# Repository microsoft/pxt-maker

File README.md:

# MakeCode Maker 

This is an experimental code editor for maker boards - try it at https://maker.makecode.com.

* [Read the docs](https://maker.makecode.com/about)

## Who is this for?

This editor is meant for micro-controllers that are friendly to breadboarding. The editor is based on [Microsoft MakeCode](https://makecode.com).

## Local Dev Server

The local server lets you to run the editor and serve the documentation from your own computer.

### Setup

1. Install [Node.js](https://nodejs.org/) 8.9.4 or higher.
2. Install [Docker](https://www.docker.com/) if you are going to edit any `.cpp` files.
3. Clone the pxt repository.
```
git clone https://github.com/microsoft/pxt
cd pxt
```
4. Install the dependencies of ``Microsoft/pxt`` and build it
```
npm install
npm run build
cd ..
```
5. Clone the ``Microsoft/pxt-common-packages`` repository
```
git clone https://github.com/microsoft/pxt-common-packages
cd pxt-common-packages
npm install
cd ..
```
6. Clone the ``Microsoft/pxt-maker`` repository
```
git clone https://github.com/microsoft/pxt-maker
cd pxt-maker
```
7. Install the PXT command line (add `sudo` for Mac/Linux shells).
```
npm install -g pxt
```
8. Install the pxt-maker dependencies.
```
npm install
```
8. Link pxt-maker back to base pxt repo (add `sudo` for Mac/Linux shells).
```
rm -Rf node_modules/pxt-core
rm -Rf node_modules/pxt-common-packages
pxt link ../pxt
pxt link ../pxt-common-packages
```

If you want to know if your folders are link, run ``ls -l``
and it will indicate them.

```
ls -l node_modules/
```

Note the above command assumes the folder structure of   
```
       maker.makecode.com
          |
  ----------------------------------
  |       |                        |
 pxt      pxt-common-packages  pxt-maker
 ```

### Refresh dal.d.ts files

Whenever you make changes to the ``#defines`` in the .cpp files, you will have to refresh
the ``dal.d.ts`` files. For that, run

```
pxt builddaldts
```

### CODAL changes

If you need to do changes to CODAL itself, follow these steps.

* create a new project in the web editor, then close the web server. Select the hardware you want to work with.
* using a command prompt, open the ``projects`` folder and find the subfolder with your new project
* open the folder in Visual Studio Code
```
code .
```
* open ``pxt.json`` and edit the dependencies to use 
the ``file:...`` path instead of ``*``

```
   dependencies: {
        "adafruit-metro-m0-express": "file:../../libs/adafruit-metro-m0-express"
   }
```
* from the command line, set the ``PXT_NODOCKER`` environment variable to ``1``

```
export PXT_NODOCKER=1
```

* run a local build that will create a CODAL checkout automatically. 
If you are missing tools, you will be notified by the build script.

```
pxt build --local --force
```

* go to the ``built/dockercodal`` folder and open all CODAL in a new Visual Studio Code instance

```
cd built/dockercodal
code libraries/*
```

* go to the Git tab in VS Code, and change the branch of the CODAL repository to work on to ``master``. You can create a new branch to start doing your work and pull requests.

* to build CODAL directly, run ``built/codal``
```
python build.py
```

* to rebuild your project from pxt, run ``pxt build --local --force`` from the project folder

### Running

Run this command from inside pxt-maker to open a local web server
```
pxt serve
```
If the local server opens in the wrong browser, make sure to copy the URL containing the local token. 
Otherwise, the editor will not be able to load the projects.

If you need to modify the `.cpp` files (and have installed yotta), enable yotta compilation using the `--localbuild` flag:
```
pxt serve --localbuild
```

### Updates

Make sure to pull changes from all repos regularly. More instructions are at https://github.com/microsoft/pxt#running-a-target-from-localhost

## Repos 

The pxt-maker target depends on several other repos. The main ones are:
- https://github.com/microsoft/pxt, the PXT framework
- https://github.com/microsoft/pxt-commmon-packages, common APIs accross various MakeCode editors
- https://github.com/lancaster-university/codal-core, CODAL core project
- https://github.com/lancaster-university/codal-mbed, mbed layer
- https://github.com/lancaster-university/codal-samd21, CODAL SAMD21 layer
- https://github.com/lancaster-university/codal-circuit-playground, Adafruit CPX layer

## Code of Conduct

This project has adopted the [Microsoft Open Source Code of Conduct](https://opensource.microsoft.com/codeofconduct/). For more information see the [Code of Conduct FAQ](https://opensource.microsoft.com/codeofconduct/faq/) or contact [opencode@microsoft.com](mailto:opencode@microsoft.com) with any additional questions or comments.

# Contributing

This project welcomes contributions and suggestions.  Most contributions require you to agree to a
Contributor License Agreement (CLA) declaring that you have the right to, and actually do, grant us
the rights to use your contribution. For details, visit https://cla.microsoft.com.

When you submit a pull request, a CLA-bot will automatically determine whether you need to provide
a CLA and decorate the PR appropriately (e.g., label, comment). Simply follow the instructions
provided by the bot. You will only need to do this once across all repos using our CLA.

This project has adopted the [Microsoft Open Source Code of Conduct](https://opensource.microsoft.com/codeofconduct/).
For more information see the [Code of Conduct FAQ](https://opensource.microsoft.com/codeofconduct/faq/) or
contact [opencode@microsoft.com](mailto:opencode@microsoft.com) with any additional questions or comments.

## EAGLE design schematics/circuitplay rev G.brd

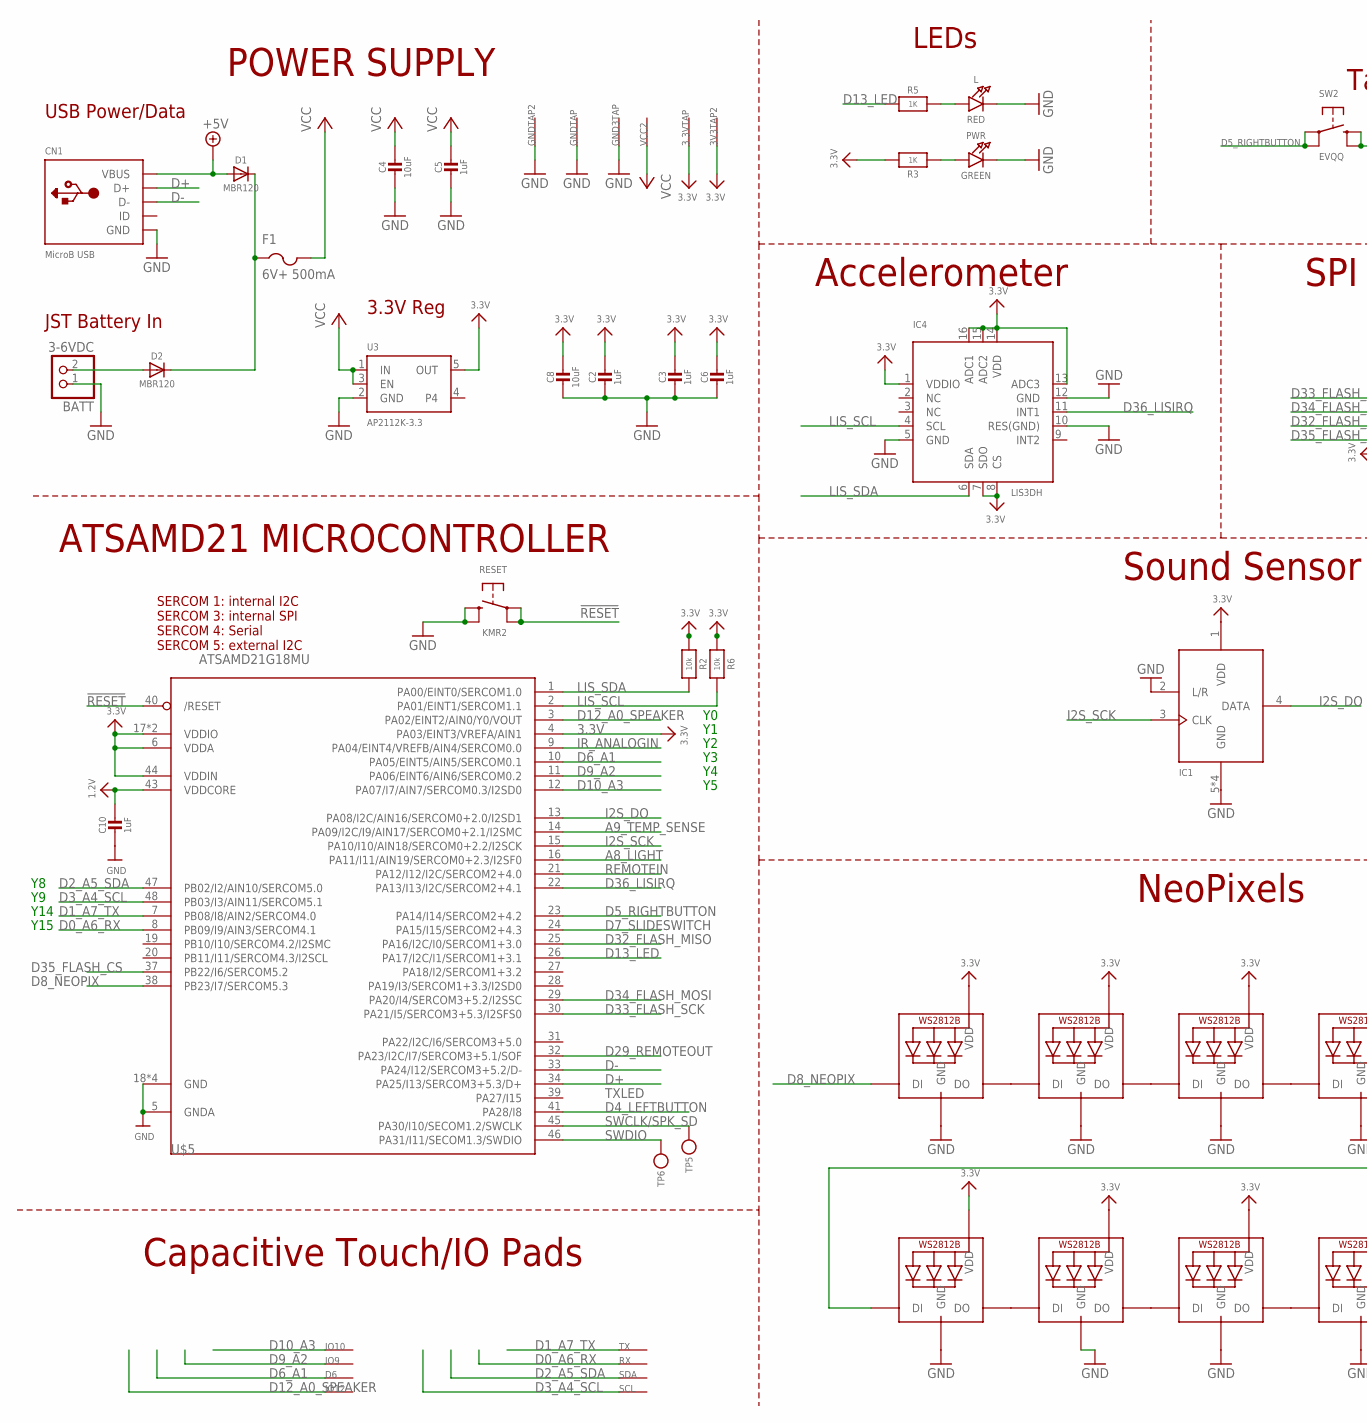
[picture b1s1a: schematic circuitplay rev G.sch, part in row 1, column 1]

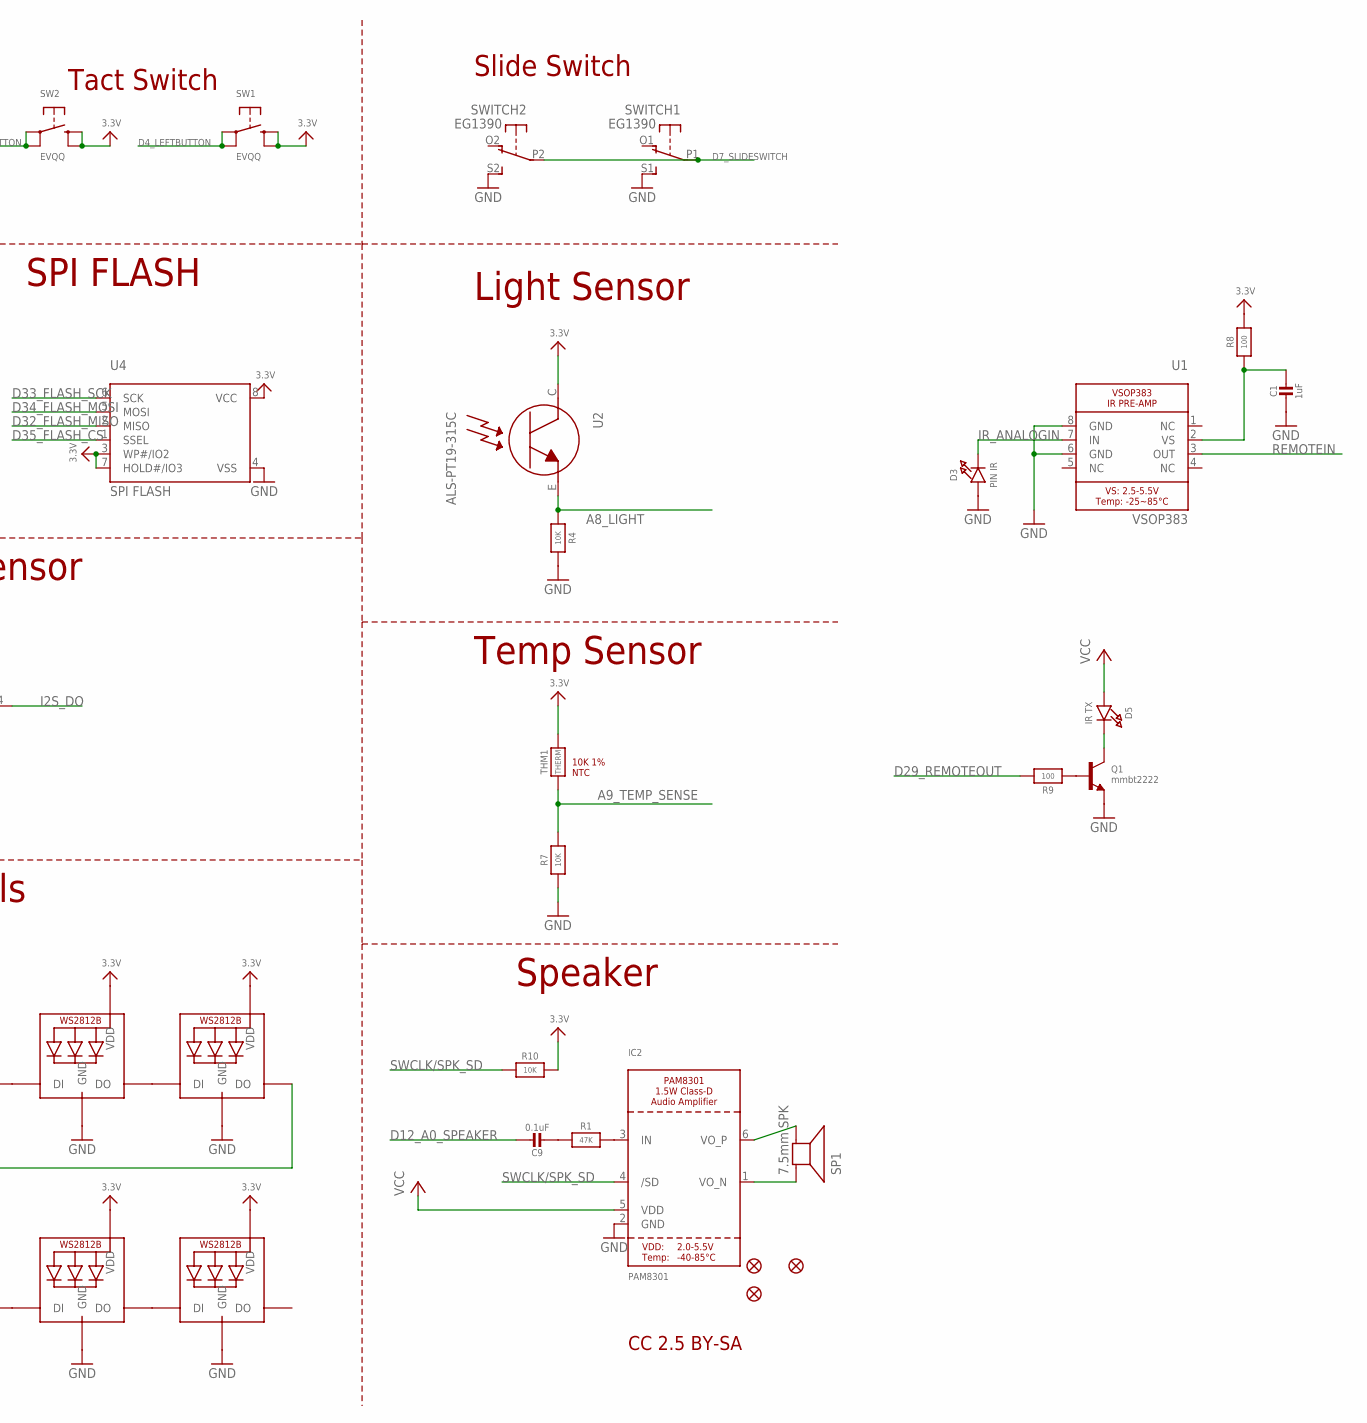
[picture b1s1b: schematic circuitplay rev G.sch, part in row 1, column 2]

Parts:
3.3VTAP, 3V3TAP2: SEWTAP-ALLIGATOR; SEWALLI
BATT: 3-6VDC; JSTPH2
C1, C2, C3, C5, C6, C10: 1uF; 0603-NO
C4, C8: 10uF; 0805-NO
C9: 0.1uF; 0603-NO
CN1: MicroB USB; 4UCONN_20329_V2
D1, D2: MBR120; SOD-123
D3: PIN IR; CHIPLED_1206_NOOUTLINE
D5: IR TX; CHIPLED_1206_NOOUTLINE
D6: SEWTAP-ALLIGATOR; SEWALLI
F1: 6V+ 500mA; R1206
GND3TAP: SEWTAP-ALLIGATOR; SEWALLI
GNDTAP, GNDTAP2: SEWTAP-ALLIGATOR; SEWALLI
IC1: MIC_PDM; SPK0415HM4H
IC2: PAM8301; SOT23-6
IC4: LIS3DH; LGA16_3X3MM
IO9, IO10, IO12: SEWTAP-ALLIGATOR; SEWALLI
L: RED; CHIPLED_0805_NOOUTLINE
LED1, LED2, LED3, LED4, LED5, LED6, LED7, LED8, LED9, LED10: WS2812B3535; LED3535
PWR: GREEN; CHIPLED_0805_NOOUTLINE
Q1: mmbt2222; SOT23-R
R1: 47K; 0603-NO
R2, R6: 10k; 0603-NO
R3, R5: 1K; 0603-NO
R4, R7, R10: 10K; 0603-NO
R8, R9: 100; 0603-NO
RESET: KMR2; BTN_KMR2_4.6X2.8
RX: SEWTAP-ALLIGATOR; SEWALLI
SCL: SEWTAP-ALLIGATOR; SEWALLI
SDA: SEWTAP-ALLIGATOR; SEWALLI
SP1: 7.5mm SPK; BUZZER_SMT_7.5MM
SW1, SW2: EVQQ; EVQ-Q2_SMALLER
SWITCH: EG1390
THM1: THERM; _0402
TP5, TP6: TESTPOINTROUND1.5MM; TESTPOINT_ROUND_1.5MM
TX: SEWTAP-ALLIGATOR; SEWALLI
U1: VSOP383
U2: ALS-PT19-315C
U3: AP2112K-3.3; SOT23-5
U4: SPI FLASH; SOIC8_150MIL
U$2, U$3, U$6: FIDUCIAL_1MM
U$5: ATSAMD21G18MU; TQFN48_7MM
VCC2: SEWTAP-ALLIGATOR; SEWALLI

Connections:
1.2V: C10.1, U$5.43 (VDDCORE)
3.3V: 3.3VTAP.P$1, 3V3TAP2.P$1, C2.1, C3.1, C6.1, C8.1, IC1.1 (VDD), IC4.1 (VDDIO), IC4.7 (SDO), IC4.8 (CS), IC4.13 (ADC3), IC4.14 (VDD), IC4.15 (ADC2), IC4.16 (ADC1), LED1.2 (VDD), LED2.2 (VDD), LED3.2 (VDD), LED4.2 (VDD), LED5.2 (VDD), LED6.2 (VDD), LED7.2 (VDD), LED8.2 (VDD), LED9.2 (VDD), LED10.2 (VDD), R2.1, R3.2, R6.1, R8.2, R10.2, SW1.B (S), SW1.B' (S1), SW2.B (S), SW2.B' (S1), THM1.2, U2.C, U3.5 (OUT), U4.3 (WP#/IO2), U4.7 (HOLD#/IO3), U4.8 (VCC), U$5.4 (PA03/EINT3/VREFA/AIN1), U$5.6 (VDDA), U$5.17 (VDDIO), U$5.36 (VDDIO), U$5.44 (VDDIN)
!RESET: RESET.A, RESET.A' (P1), U$5.40 (/RESET)
+5V: CN1.VBUS, D1.A
A8_LIGHT: R4.2, U2.E, U$5.16 (PA11/I11/AIN19/SERCOM0+2.3/I2SF0)
A9_TEMP_SENSE: R7.2, THM1.1, U$5.14 (PA09/I2C/I9/AIN17/SERCOM0+2.1/I2SMC)
D0_A6_RX: RX.P$1, U$5.8 (PB09/I9/AIN3/SERCOM4.1)
D1_A7_TX: TX.P$1, U$5.7 (PB08/I8/AIN2/SERCOM4.0)
D2_A5_SDA: SDA.P$1, U$5.47 (PB02/I2/AIN10/SERCOM5.0)
D3_A4_SCL: SCL.P$1, U$5.48 (PB03/I3/AIN11/SERCOM5.1)
D4_LEFTBUTTON: SW1.A, SW1.A' (P1), U$5.41 (PA28/I8)
D5_RIGHTBUTTON: SW2.A, SW2.A' (P1), U$5.23 (PA14/I14/SERCOM2+4.2)
D6_A1: D6.P$1, U$5.10 (PA05/EINT5/AIN5/SERCOM0.1)
D7_SLIDESWITCH: SWITCH.P1, SWITCH.P2, U$5.24 (PA15/I15/SERCOM2+4.3)
D8_NEOPIX: LED6.1 (DI), U$5.38 (PB23/I7/SERCOM5.3)
D9_A2: IO9.P$1, U$5.11 (PA06/EINT6/AIN6/SERCOM0.2)
D10_A3: IO10.P$1, U$5.12 (PA07/I7/AIN7/SERCOM0.3/I2SD0)
D12_A0_SPEAKER: C9.1, IO12.P$1, U$5.3 (PA02/EINT2/AIN0/Y0/VOUT)
D13_LED: R5.1, U$5.26 (PA17/I2C/I1/SERCOM1+3.1)
D29_REMOTEOUT: R9.2, U$5.32 (PA23/I2C/I7/SERCOM3+5.1/SOF)
D32_FLASH_MISO: U4.2 (MISO), U$5.25 (PA16/I2C/I0/SERCOM1+3.0)
D33_FLASH_SCK: U4.6 (SCK), U$5.30 (PA21/I5/SERCOM3+5.3/I2SFS0)
D34_FLASH_MOSI: U4.5 (MOSI), U$5.29 (PA20/I4/SERCOM3+5.2/I2SSC)
D35_FLASH_CS: U4.1 (SSEL), U$5.37 (PB22/I6/SERCOM5.2)
D36_LISIRQ: IC4.11 (INT1), U$5.22 (PA13/I13/I2C/SERCOM2+4.1)
D+: CN1.D+, U$5.34 (PA25/I13/SERCOM3+5.3/D+)
D-: CN1.D-, U$5.33 (PA24/I12/SERCOM3+5.2/D-)
GND: BATT.1, C1.2, C2.2, C3.2, C4.2, C5.2, C6.2, C8.2, C10.2, CN1.BASE@1 (GND), CN1.BASE@2 (GND), CN1.GND, CN1.SPRT@1 (GND), CN1.SPRT@2 (GND), CN1.SPRT@3 (GND), CN1.SPRT@4 (GND), D3.A, GND3TAP.P$1, GNDTAP.P$1, GNDTAP2.P$1, IC1.2 (L/R), IC1.5 (GND), IC1.6 (GND), IC1.7 (GND), IC1.8 (GND), IC2.2 (GND), IC4.5 (GND), IC4.10 (RES(GND)), IC4.12 (GND), L.C, LED1.4 (GND), LED2.4 (GND), LED3.4 (GND), LED4.4 (GND), LED5.4 (GND), LED6.4 (GND), LED7.4 (GND), LED8.4 (GND), LED9.4 (GND), LED10.4 (GND), PWR.C, Q1.2 (E), R4.1, R7.1, RESET.B (S), RESET.B' (S1), SWITCH.S1 (S), SWITCH.S2 (S), U1.6 (GND), U1.8 (GND), U3.2 (GND), U4.4 (VSS), U$5.5 (GNDA), U$5.18 (GND), U$5.35 (GND), U$5.42 (GND), U$5.THERMAL (GND)
I2S_DO: IC1.4 (DATA), U$5.13 (PA08/I2C/AIN16/SERCOM0+2.0/I2SD1)
I2S_SCK: IC1.3 (CLK), U$5.15 (PA10/I10/AIN18/SERCOM0+2.2/I2SCK)
IR_ANALOGIN: D3.C, U1.7 (IN), U$5.9 (PA04/EINT4/VREFB/AIN4/SERCOM0.0)
LIS_SCL: IC4.4 (SCL), R6.2, U$5.2 (PA01/EINT1/SERCOM1.1)
LIS_SDA: IC4.6 (SDA), R2.2, U$5.1 (PA00/EINT0/SERCOM1.0)
unnamed: PWR.A, R3.1
unnamed: C1.1, R8.1, U1.2 (VS)
unnamed: D1.C, D2.C, F1.1
unnamed: Q1.1 (B), R9.1
unnamed: C9.2, R1.1
unnamed: BATT.2, D2.A
unnamed: IC2.3 (IN), R1.2
unnamed: IC2.6 (VO_P), SP1.-
unnamed: L.A, R5.2
unnamed: LED1.1 (DI), LED2.3 (DO)
unnamed: LED1.3 (DO), LED3.1 (DI)
unnamed: LED2.1 (DI), LED10.3 (DO)
unnamed: LED6.3 (DO), LED7.1 (DI)
unnamed: IC2.1 (VO_N), SP1.+
unnamed: LED7.3 (DO), LED8.1 (DI)
unnamed: LED8.3 (DO), LED9.1 (DI)
unnamed: LED9.3 (DO), LED10.1 (DI)
unnamed: LED3.3 (DO), LED4.1 (DI)
unnamed: LED4.3 (DO), LED5.1 (DI)
unnamed: D5.C, Q1.3 (C)
REMOTEIN: U1.3 (OUT), U$5.21 (PA12/I12/I2C/SERCOM2+4.0)
SWCLK/SPK_SD: IC2.4 (/SD), R10.1, TP5.P$1, U$5.45 (PA30/I10/SECOM1.2/SWCLK)
SWDIO: TP6.P$1, U$5.46 (PA31/I11/SECOM1.3/SWDIO)
VCC: C4.1, C5.1, D5.A, F1.2, IC2.5 (VDD), U3.1 (IN), U3.3 (EN), VCC2.P$1

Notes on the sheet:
CC 2.5 BY-SA
10K 1% NTC
ATSAMD21 MICROCONTROLLER
USB Power/Data
JST Battery In
3.3V Reg
POWER SUPPLY
NeoPixels
Speaker
Temp Sensor
Light Sensor
Sound Sensor
Slide Switch
Tact Switch
LEDs
Accelerometer
TXLED
SERCOM 1: internal I2C SERCOM 3: internal SPI SERCOM 4: Serial SERCOM 5: external I2C
Y14
Y15
Capacitive Touch/IO Pads
SPI FLASH

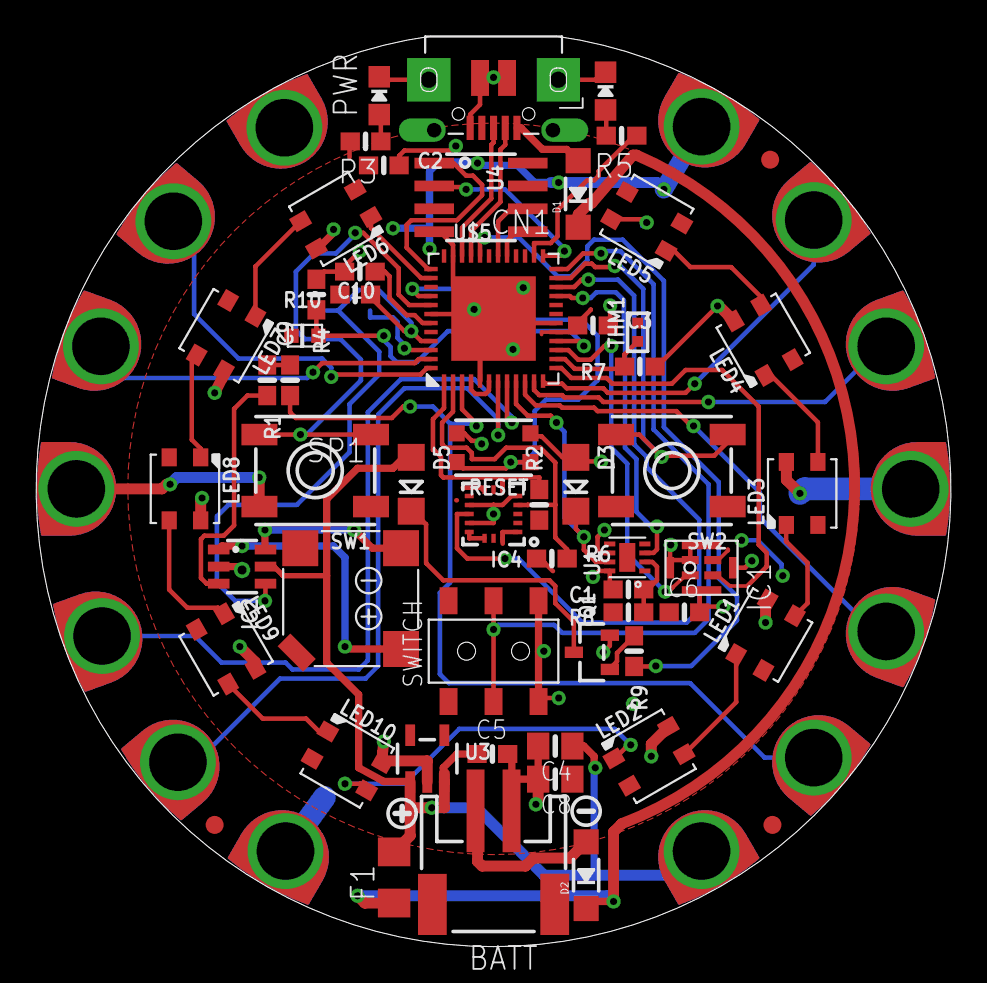
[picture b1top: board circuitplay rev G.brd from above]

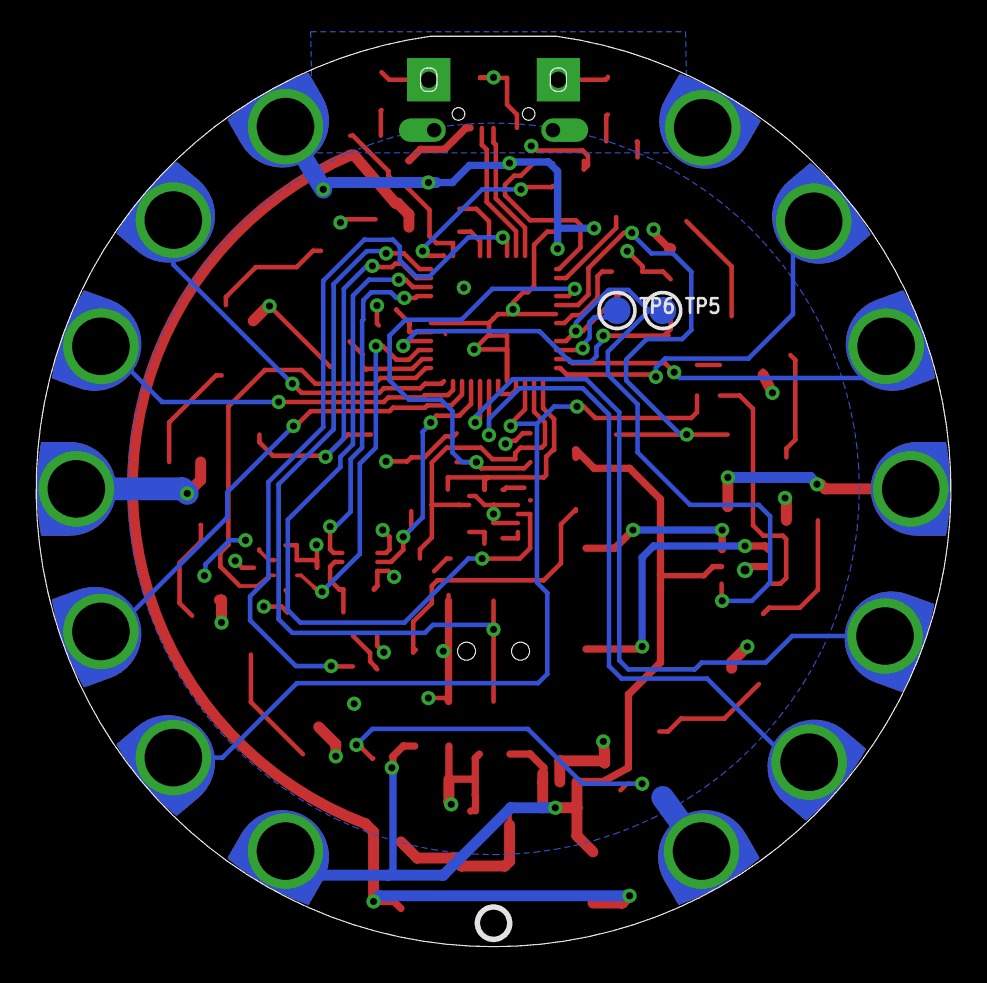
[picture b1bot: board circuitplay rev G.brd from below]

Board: 2 copper layers, 50.8 x 50.6 mm, 78 parts (5 on the bottom side), 57 nets.

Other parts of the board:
U$1: SYMBOL_MINUS
U$4: FLORAMED
U$7: PCBFEAT-REV-040
U$16: CPLAY_EXPRESS_FRONT_REVG
U$35: SYMBOL_PLUS
U$46: CPLAY_EXPRESS_BACK_REVD

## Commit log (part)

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2020-11-08 0.13.64
2020-11-20 Add esp32-devkitc
2020-11-24 Docker fix
2020-11-25 Clean up config
2020-11-25 Disable FXOS8700 accel for now (changed APIs in codal)
2020-11-25 Add accel lib to brain
2020-11-27 bump pxt-core to 6.6.15, bump pxt-common-packages to 8.3.3
2020-11-27 bump pxt-core to 6.6.16
2020-11-30 Bump nrf52 codal to 1.1.8
2020-12-01 Use fresh random BL cfg keys for light power pins
2020-12-01 Bump pxt-c-p to 8.3.4
2020-12-01 support for JD brain nrf52840 (#319)
    * Initial support for brain
    * Clean up config
    * Disable FXOS8700 accel for now (changed APIs in codal)
    * Re-generate
    * Add accel lib to brain
    * Bump nrf52 codal to 1.1.8
2020-12-02 Fixes for brain board
2020-12-02 0.13.67
2020-12-02 Try to make the brain sim work with neopixels
2020-12-07 bump pxt-core to 6.7.1, bump pxt-common-packages to 8.3.5
2020-12-07 0.13.68
2020-12-08 0.14.1
2020-12-08 updated target config
2020-12-09 adding sim
2020-12-10 updated schema
2020-12-10 updated sims
2020-12-10 add debug url
2020-12-10 External simulators, support for jacdac (#322)
    * adding sim
    * fix led
    * updated schema
    * updated sims
    * updated orl
    * add debug url
2020-12-10 0.14.2
2020-12-11 bump pxt-core to 6.7.4, bump pxt-common-packages to 8.3.7
2020-12-11 0.14.3
2020-12-14 bum pxt
2020-12-14 upgrade to jacdac hw sim (#323)
    * upgrade to jacdac hw sim
    * bum pxt
2020-12-14 bump pxt-common-packages to 8.4.3
2020-12-14 0.14.5
2020-12-14 bump pxt-core to 6.8.3
2020-12-15 Bump pxt-core to 6.8.4 (better mkc support)
2020-12-15 0.14.7
2020-12-17 bump pxt-core to 6.8.6
2020-12-17 0.14.8
2020-12-18 0.14.9
2020-12-23 bump pxt-core to 6.8.10
2020-12-23 0.14.10
2020-12-29 Wrong PIN for LED defined (#326)
2021-01-11 Remove IRxx elements
    The Bluefruit has no IR-RX/-TX elements (but Bluetooth low energy)
2021-01-20 Disable device config for now on esp
2021-02-05 bump pxt-core to 6.9.8, bump pxt-common-packages to 8.5.2
2021-02-05 0.14.11
2021-03-02 permanent jacdac
2021-03-02 bump pxt-core to 6.9.16, bump pxt-common-packages to 8.5.3
2021-03-02 0.14.13
2021-03-03 bump pxt-core to 6.9.18, bump pxt-common-packages to 8.5.4
2021-03-03 0.14.15
2021-03-03 add machachi board
2021-03-03 add machachi board (#332)
    * add machachi board
    * update README
2021-03-03 0.14.16
2021-03-03 update pin map for machachi
2021-03-03 update pin map for machachi (#333)
    * update pin map for machachi
    * use camelcase for button names
2021-03-03 0.14.17
2021-03-03 use P0_7 for JACK_TX
2021-03-03 update JACK_TX pin for machachi
2021-03-03 0.14.19
2021-03-04 0.14.20
2021-03-05 updated sim location
2021-03-05 0.14.21
2021-03-05 updated approved exnteion path
2021-03-08 bump pxt-core to 6.9.25
2021-03-12 bump pxt-core to 6.11.2, bump pxt-common-packages to 8.7.1
2021-03-12 0.14.23
2021-03-15 Update adafruit.md (#336)
    Add info for Adafruit Grand Central M4 express so it can appear on makecode's homepage
2021-03-16 bump to es2017
2021-03-16 updated package versions
2021-03-16 more attempts at fixing
2021-03-16 miracle import fixing
2021-03-16 0.14.24
2021-03-16 bump minor
2021-04-10 update adafruit-grand-central-express-m4 pins.
    - changed layout for easier maintainability
    - added flash pins
    - added JACK_TX to enable serial
2021-04-10 updated adafruit-grand-central-m4 features
    - added more features
    - updated bootloader URL
2021-04-11 bump pxt-core to 6.13.17, bump pxt-common-packages to 8.9.5
2021-04-26 add makeable target
2021-04-26 undo bad changes to pxtarget.json
2021-04-26 update adafruit-grand-central-express-m4 pins. (#340)
    - changed layout for easier maintainability
    - added flash pins
    - added JACK_TX to enable serial
2021-04-26 bump pxt-core to 6.13.25, bump pxt-common-packages to 8.9.6
2021-04-28 Correct flashEnd value
2021-04-28 add makeable to libs
2021-04-28 correct path
2021-04-28 bump makeable target and update flashend
2021-04-28 0.15.4
2021-05-10 bump cp
2021-05-11 fixup pxtarget.json for build
2021-05-11 Add Makeable board. (#342)
    * add makeable target
    * update board svg and pxtarget.json
    * undo bad changes to pxtarget.json
    * update readme
    * Correct flashEnd value
    * add makeable to libs
2021-05-11 Add analog pin to ensure blocks can be populated
2021-05-11 0.15.6
2021-05-11 0.15.7
2021-05-11 bump pxt-core to 6.13.28, bump pxt-common-packages to 8.9.9
2021-05-11 0.15.8
2021-05-12 bump makeable
2021-05-12 0.15.9
2021-05-12 0.15.10
2021-05-13 bump makeable (#343)
2021-05-13 bump makeable to remove usb ep timeout
2021-05-13 0.15.12
2021-05-19 bump pxt-core to 6.13.34, bump pxt-common-packages to 8.9.11
2021-05-20 attempt at fixing game
2021-05-20 0.15.14
2021-06-14 update pinout for makeable board
2021-06-14 update pin map
2021-06-15 Add new esp32s2 compile service
2021-06-15 bump pxt-core to 6.13.53, bump pxt-common-packages to 8.9.14
2021-06-15 0.15.15
2021-06-17 0.15.16
2021-07-14 add jacdac-iot board
2021-07-23 update shims
2021-07-26 enable pins on esp32
2021-08-02 fix pin config
2021-08-04 fix deps
2021-08-04 add missing libs
2021-08-04 Add cards for ESP32 boards
2021-08-04 Optimised images with calibre/image-actions
2021-08-05 add support for esp32 and esp32-s2 (#347)
    * Add esp32-devkitc
    * Docker fix
    * Disable device config for now on esp
    * Add esp32s2
    * Add new esp32s2 compile service
    * add jacdac-iot board
2021-08-05 0.15.17
2021-08-17 Makeable->JacdacNRFBrain
2021-09-01 Bump pxt-c-p to 9.2.2
2021-09-01 0.15.18
2021-09-03 0.15.19
2021-09-04 bump pxt-core to 7.2.9, bump pxt-common-packages to 9.2.5
2021-09-10 0.15.21
2021-09-10 0.15.22
2021-09-14 unify lib name and pxt.json name
2021-09-20 0.15.23
2021-09-21 Start on rp2040 (rpi pico) support
2021-09-22 0.15.24
2021-09-22 updated semantic-less version
2021-09-22 theme fixing
2021-09-22 start on jacdac
2021-09-22 Bump codal stm32 to 1.3.4 fixes https://github.com/microsoft/jacdac/issues/666
2021-09-24 bump pxt-core to 7.2.19
2021-09-24 0.15.27
2021-09-28 use generic board image
2021-09-28 add jacdac brain boards
2021-09-28 Bump codal pico and p-c-p
2021-09-29 Fix typo
2021-09-29 add a hack
2021-09-29 0.15.28
2021-09-29 0.15.29
2021-09-30 Add bootloader_board_id for jacdac boards lacking it
2021-09-30 Fix rp2040 crash
2021-09-30 0.15.31
2021-09-30 0.15.32
2021-10-04 Fix RGB config on s2 brain
2021-10-05 Bump codal rp2040
2021-10-05 0.15.34
2021-10-05 Add jacdac._setLedChannel() sim
2021-10-06 update package-lock
2021-10-06 slight reorg of maker to support jacdac modules
2021-10-06 0.15.36
2021-10-07 Bump pxt-c-p to 9.3.3
2021-10-07 0.15.37
2021-10-19 0.15.38
2021-10-19 Bump pxt-c-p and pxt
2021-10-21 bump pxt-c-p
2021-10-21 0.15.40
2021-10-22 Update display in _setLedChannel
2021-10-22 bump p-c-p
2021-10-22 0.15.42
2021-10-22 bump pxt-core to 7.3.6
2021-10-22 0.15.43
2021-10-23 real svg for iot brain
2021-10-23 0.15.45
2021-10-23 0.15.46
2021-10-27 0.15.48
2021-10-29 updated all deps
2021-11-05 0.15.49
2021-11-05 bump pxt-core to 7.3.9, bump pxt-common-packages to 9.3.13
2021-12-01 Update common pkgs with watchdogs
2021-12-01 0.15.51
2022-01-14 Bump engine.io from 4.1.1 to 4.1.2
    Bumps [engine.io](https://github.com/socketio/engine.io) from 4.1.1 to 4.1.2.
    - [Release notes](https://github.com/socketio/engine.io/releases)
    - [Changelog](https://github.com/socketio/engine.io/blob/4.1.2/CHANGELOG.md)
    - [Commits](https://github.com/socketio/engine.io/compare/4.1.1...4.1.2)
    ---
    updated-dependencies:
2022-01-21 Bump log4js from 6.3.0 to 6.4.0
    Bumps [log4js](https://github.com/log4js-node/log4js-node) from 6.3.0 to 6.4.0.
    - [Release notes](https://github.com/log4js-node/log4js-node/releases)
    - [Changelog](https://github.com/log4js-node/log4js-node/blob/master/CHANGELOG.md)
    - [Commits](https://github.com/log4js-node/log4js-node/compare/v6.3.0...v6.4.0)
    ---
    updated-dependencies:
2022-01-27 Bump cached-path-relative from 1.0.2 to 1.1.0
    Bumps [cached-path-relative](https://github.com/ashaffer/cached-path-relative) from 1.0.2 to 1.1.0.
    - [Release notes](https://github.com/ashaffer/cached-path-relative/releases)
    - [Commits](https://github.com/ashaffer/cached-path-relative/commits)
    ---
    updated-dependencies:
    - dependency-name: cached-path-relative
2022-02-01 0.15.52
2022-02-01 0.15.53
2022-02-02 bump pxt-common-packages to 9.4.9
2022-02-02 0.15.55
2022-02-02 updated pxt
2022-02-02 updating packages
2022-02-02 0.15.57
2022-02-11 0.15.58
2022-02-15 Bump follow-redirects from 1.14.7 to 1.14.8
    Bumps [follow-redirects](https://github.com/follow-redirects/follow-redirects) from 1.14.7 to 1.14.8.
    - [Release notes](https://github.com/follow-redirects/follow-redirects/releases)
    - [Commits](https://github.com/follow-redirects/follow-redirects/compare/v1.14.7...v1.14.8)
    ---
    updated-dependencies:
    - dependency-name: follow-redirects
2022-04-22 bump codal with hid joystick fixes
2022-05-04 Adding domains.html file
2022-05-04 Bumping pxt-core to 7.5.25
2022-05-04 Bumping pxt-core to 7.5.26
2022-05-04 0.15.61
2022-05-04 0.15.62
2022-05-31 bump pxt-common-packages to 9.5.10
2022-05-31 Microsoft mandatory file
2022-05-31 0.15.63
2022-05-31 Microsoft mandatory file (#360)
2022-05-31 Bump simple-get from 3.1.0 to 3.1.1
    Bumps [simple-get](https://github.com/feross/simple-get) from 3.1.0 to 3.1.1.
    - [Release notes](https://github.com/feross/simple-get/releases)
    - [Commits](https://github.com/feross/simple-get/compare/v3.1.0...v3.1.1)
    ---
    updated-dependencies:
    - dependency-name: simple-get
2022-06-01 added aebo joystick board
2022-06-15 bump pxt-core to 7.5.52
2022-06-15 add new approvedRepoLib format
2022-06-15 add new approvedRepoLib format (#365)
2022-06-20 bump xt
2022-06-20 0.15.66
2022-11-22 Bump engine.io from 6.1.2 to 6.2.1
    Bumps [engine.io](https://github.com/socketio/engine.io) from 6.1.2 to 6.2.1.
    - [Release notes](https://github.com/socketio/engine.io/releases)
    - [Changelog](https://github.com/socketio/engine.io/blob/main/CHANGELOG.md)
    - [Commits](https://github.com/socketio/engine.io/compare/6.1.2...6.2.1)
    ---
    updated-dependencies:
2023-01-27 Bump ua-parser-js from 0.7.31 to 0.7.33
    Bumps [ua-parser-js](https://github.com/faisalman/ua-parser-js) from 0.7.31 to 0.7.33.
    - [Release notes](https://github.com/faisalman/ua-parser-js/releases)
    - [Changelog](https://github.com/faisalman/ua-parser-js/blob/master/changelog.md)
    - [Commits](https://github.com/faisalman/ua-parser-js/compare/0.7.31...0.7.33)
    ---
    updated-dependencies:
2023-05-03 Bump engine.io from 6.1.2 to 6.4.2
    Bumps [engine.io](https://github.com/socketio/engine.io) from 6.1.2 to 6.4.2.
    - [Release notes](https://github.com/socketio/engine.io/releases)
    - [Changelog](https://github.com/socketio/engine.io/blob/main/CHANGELOG.md)
    - [Commits](https://github.com/socketio/engine.io/compare/6.1.2...6.4.2)
    ---
    updated-dependencies:
2023-07-12 Bump semver from 5.7.1 to 5.7.2
    Bumps [semver](https://github.com/npm/node-semver) from 5.7.1 to 5.7.2.
    - [Release notes](https://github.com/npm/node-semver/releases)
    - [Changelog](https://github.com/npm/node-semver/blob/v5.7.2/CHANGELOG.md)
    - [Commits](https://github.com/npm/node-semver/compare/v5.7.1...v5.7.2)
    ---
    updated-dependencies:
2025-11-14 bringing pxt-maker up-to-date (#385)
    * maker update
    * changes from Richard
    * new jacdac
2025-11-14 port over github actions from pxt-microbit (#386)
2025-11-14 [pxt-cli] bump version to v0.15.67
2025-11-14 [pxt-cli] bump version to v0.15.67 (#387)
2026-03-12 Add CodeQL analysis workflow configuration
2026-03-12 [pxt-cli] bump version to v0.15.68 (#388)
2026-03-12 [pxt-cli] bump version to v0.15.69 (#389)
2026-03-12 move jacdac forward
2026-03-13 updates suggested from richard
2026-03-13 fix missing }
2026-03-13 move jacdac forward (#390)
    * move jacdac forward
    * updates
    * update and fix compile errors
    * updates suggested from richard
    * fix missing }
2026-03-13 [pxt-cli] bump version to v0.15.70 (#391)

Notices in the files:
parts and their libraries:
microbuilder: This work is placed in the public domain, and may be freely used for commercial and non-commercial work with the following conditions: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
